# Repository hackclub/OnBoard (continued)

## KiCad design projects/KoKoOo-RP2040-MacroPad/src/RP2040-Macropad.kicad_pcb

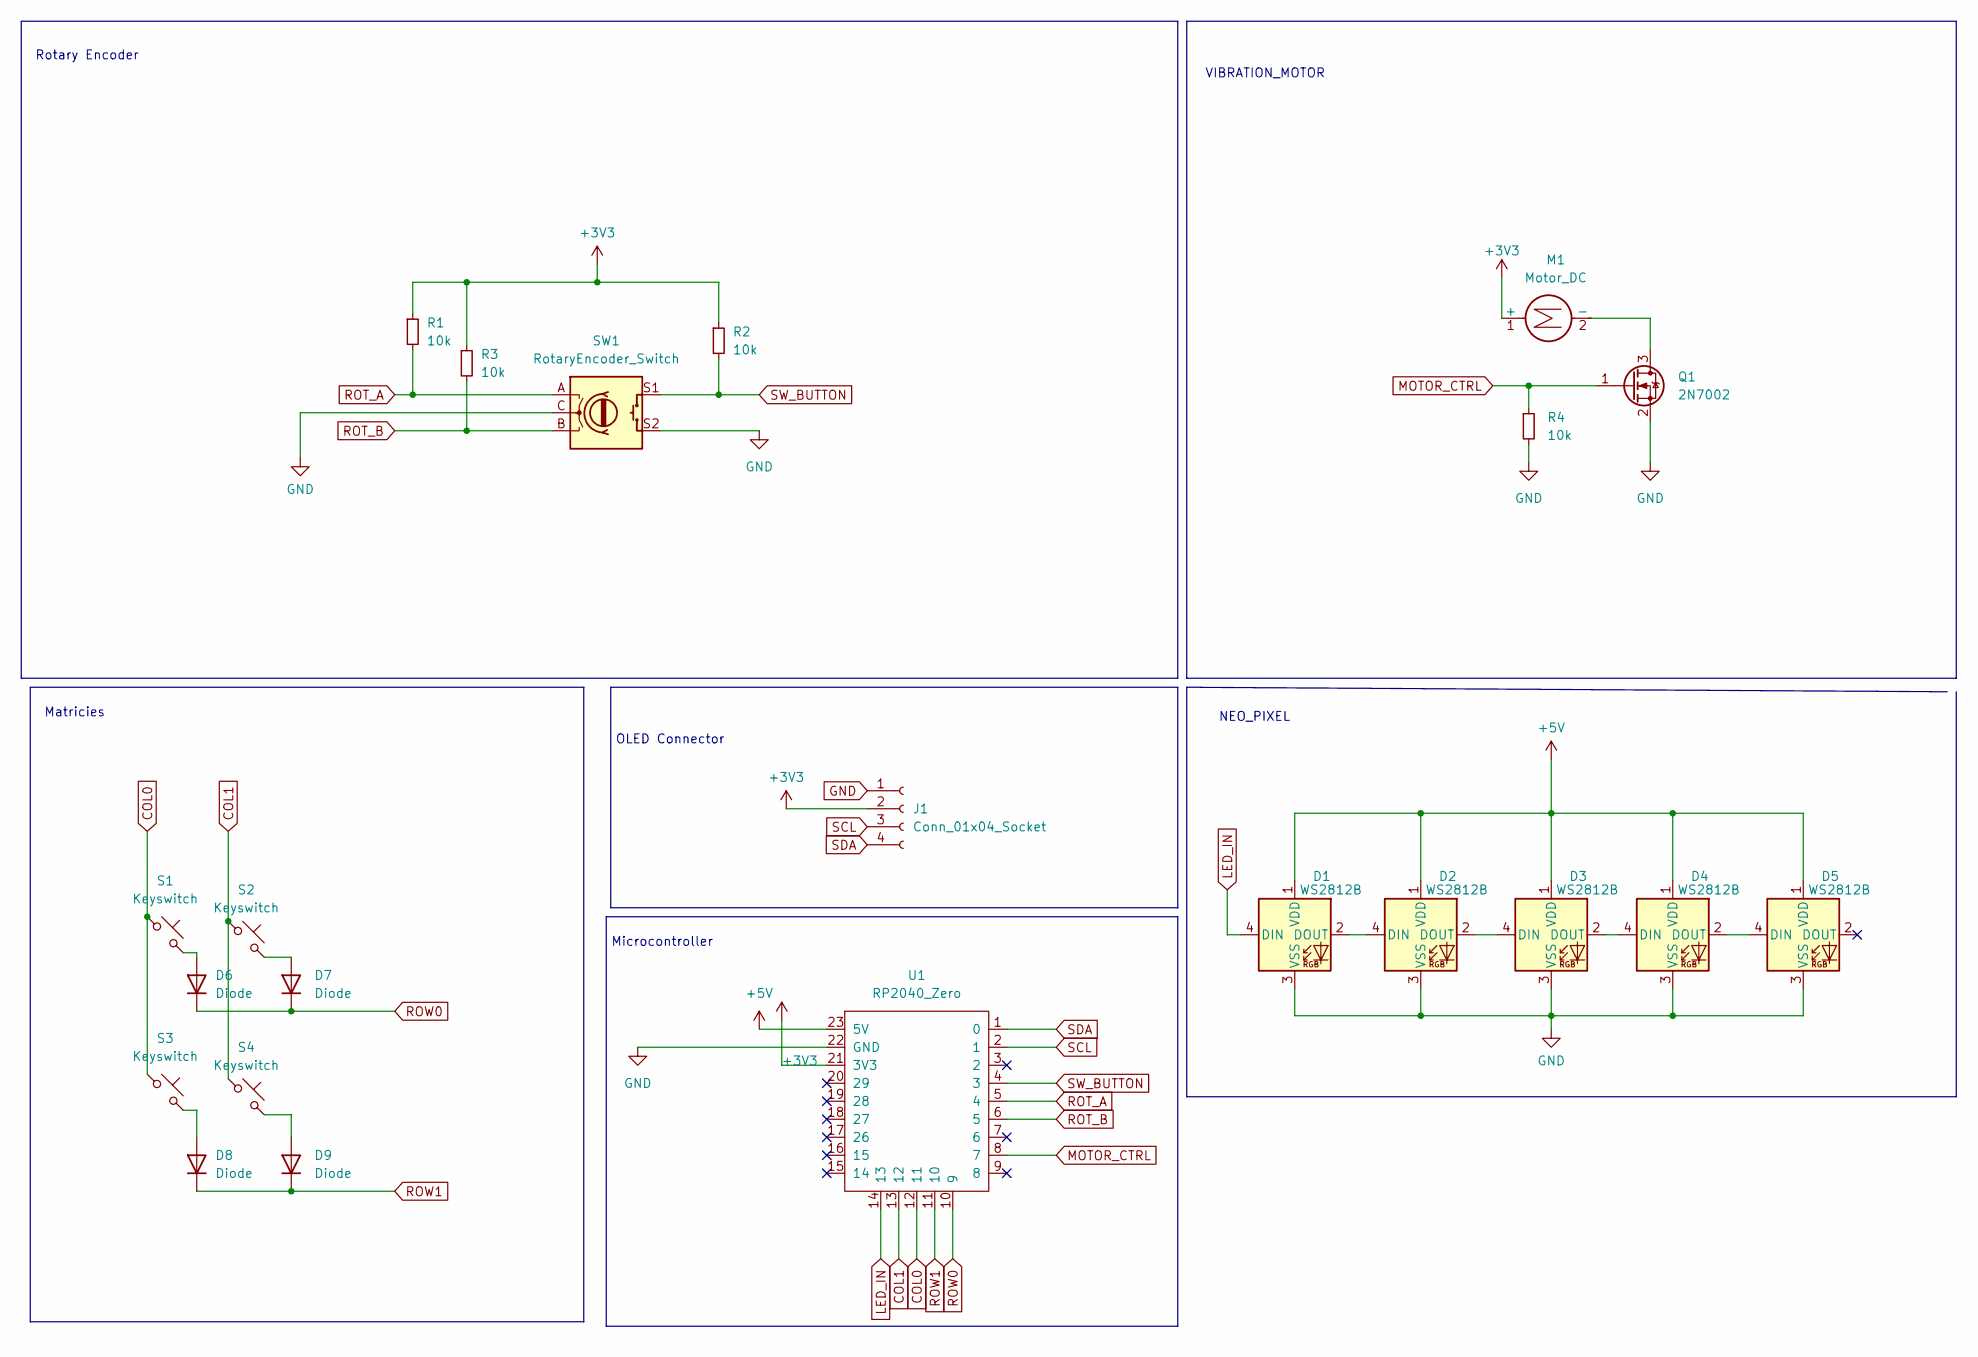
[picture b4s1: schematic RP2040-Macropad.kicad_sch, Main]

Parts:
D1, D2, D3, D4, D5: WS2812B; LED-WS2812BF5
D6, D7, D8, D9: Diode; Diode_SOD-123
J1: Conn_01x04_Socket; PinSocket_1x04_P2.54mm_Vertical
M1: Motor_DC; VC0820B006F
Q1: 2N7002; SOT-23
R1, R2, R3, R4: 10k; R_0805_2012Metric
S1, S2, S3, S4: Keyswitch; MX_Plate
SW1: RotaryEncoder_Switch; RotaryEncoder_Alps_EC11E-Switch_Vertical_H20mm
U1: RP2040_Zero

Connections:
+3V3: J1.2, M1.1 (+), R1.1, R2.1, R3.1, U1.21 (3V3)
+5V: D1.1 (VDD), D2.1 (VDD), D3.1 (VDD), D4.1 (VDD), D5.1 (VDD), U1.23 (5V)
COL0: S1.1, S3.1, U1.12 (11)
COL1: S2.1, S4.1, U1.13 (12)
GND: D1.3 (VSS), D2.3 (VSS), D3.3 (VSS), D4.3 (VSS), D5.3 (VSS), J1.1, Q1.2 (S), R4.2, SW1.C, SW1.S2, U1.22 (GND)
LED_IN: D1.4 (DIN), U1.14 (13)
MOTOR_CTRL: Q1.1 (G), R4.1, U1.8 (7)
unnamed: D1.2 (DOUT), D2.4 (DIN)
unnamed: D2.2 (DOUT), D3.4 (DIN)
unnamed: D3.2 (DOUT), D4.4 (DIN)
unnamed: D4.2 (DOUT), D5.4 (DIN)
unnamed: D6.2 (A), S1.2
unnamed: D7.2 (A), S2.2
unnamed: D8.2 (A), S3.2
unnamed: D9.2 (A), S4.2
unnamed: M1.2 (-), Q1.3 (D)
ROT_A: R1.2, SW1.A, U1.5 (4)
ROT_B: R3.2, SW1.B, U1.6 (5)
ROW0: D6.1 (K), D7.1 (K), U1.10 (9)
ROW1: D8.1 (K), D9.1 (K), U1.11 (10)
SCL: J1.3, U1.2 (1)
SDA: J1.4, U1.1 (0)
SW_BUTTON: R2.2, SW1.S1, U1.4 (3)

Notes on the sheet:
Matricies
NEO_PIXEL
Rotary Encoder
OLED Connector
Microcontroller
VIBRATION_MOTOR

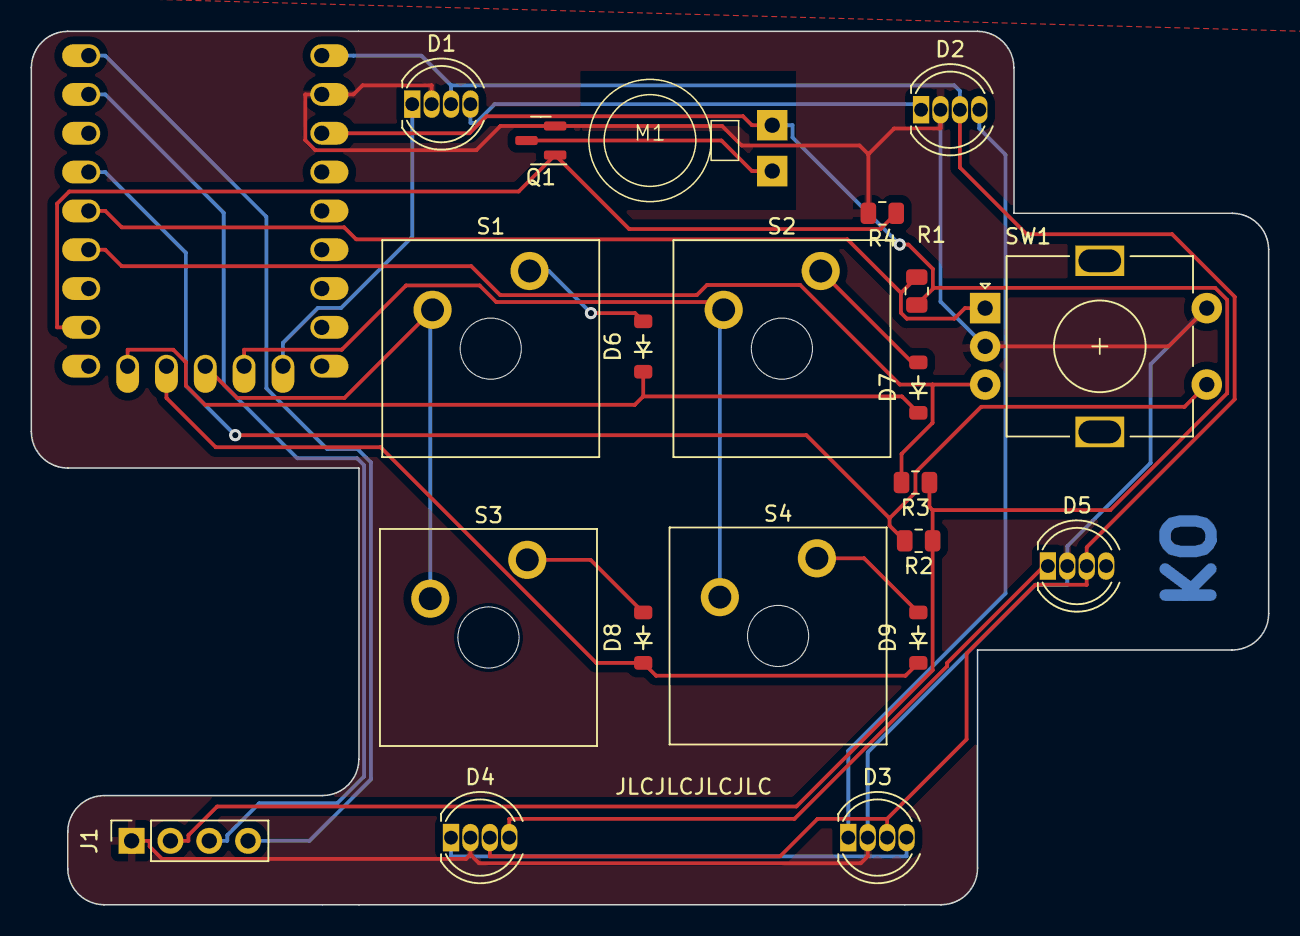
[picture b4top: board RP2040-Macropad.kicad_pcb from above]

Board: 2 copper layers, 81.0 x 57.2 mm, 22 parts (1 on the bottom side), 23 nets.

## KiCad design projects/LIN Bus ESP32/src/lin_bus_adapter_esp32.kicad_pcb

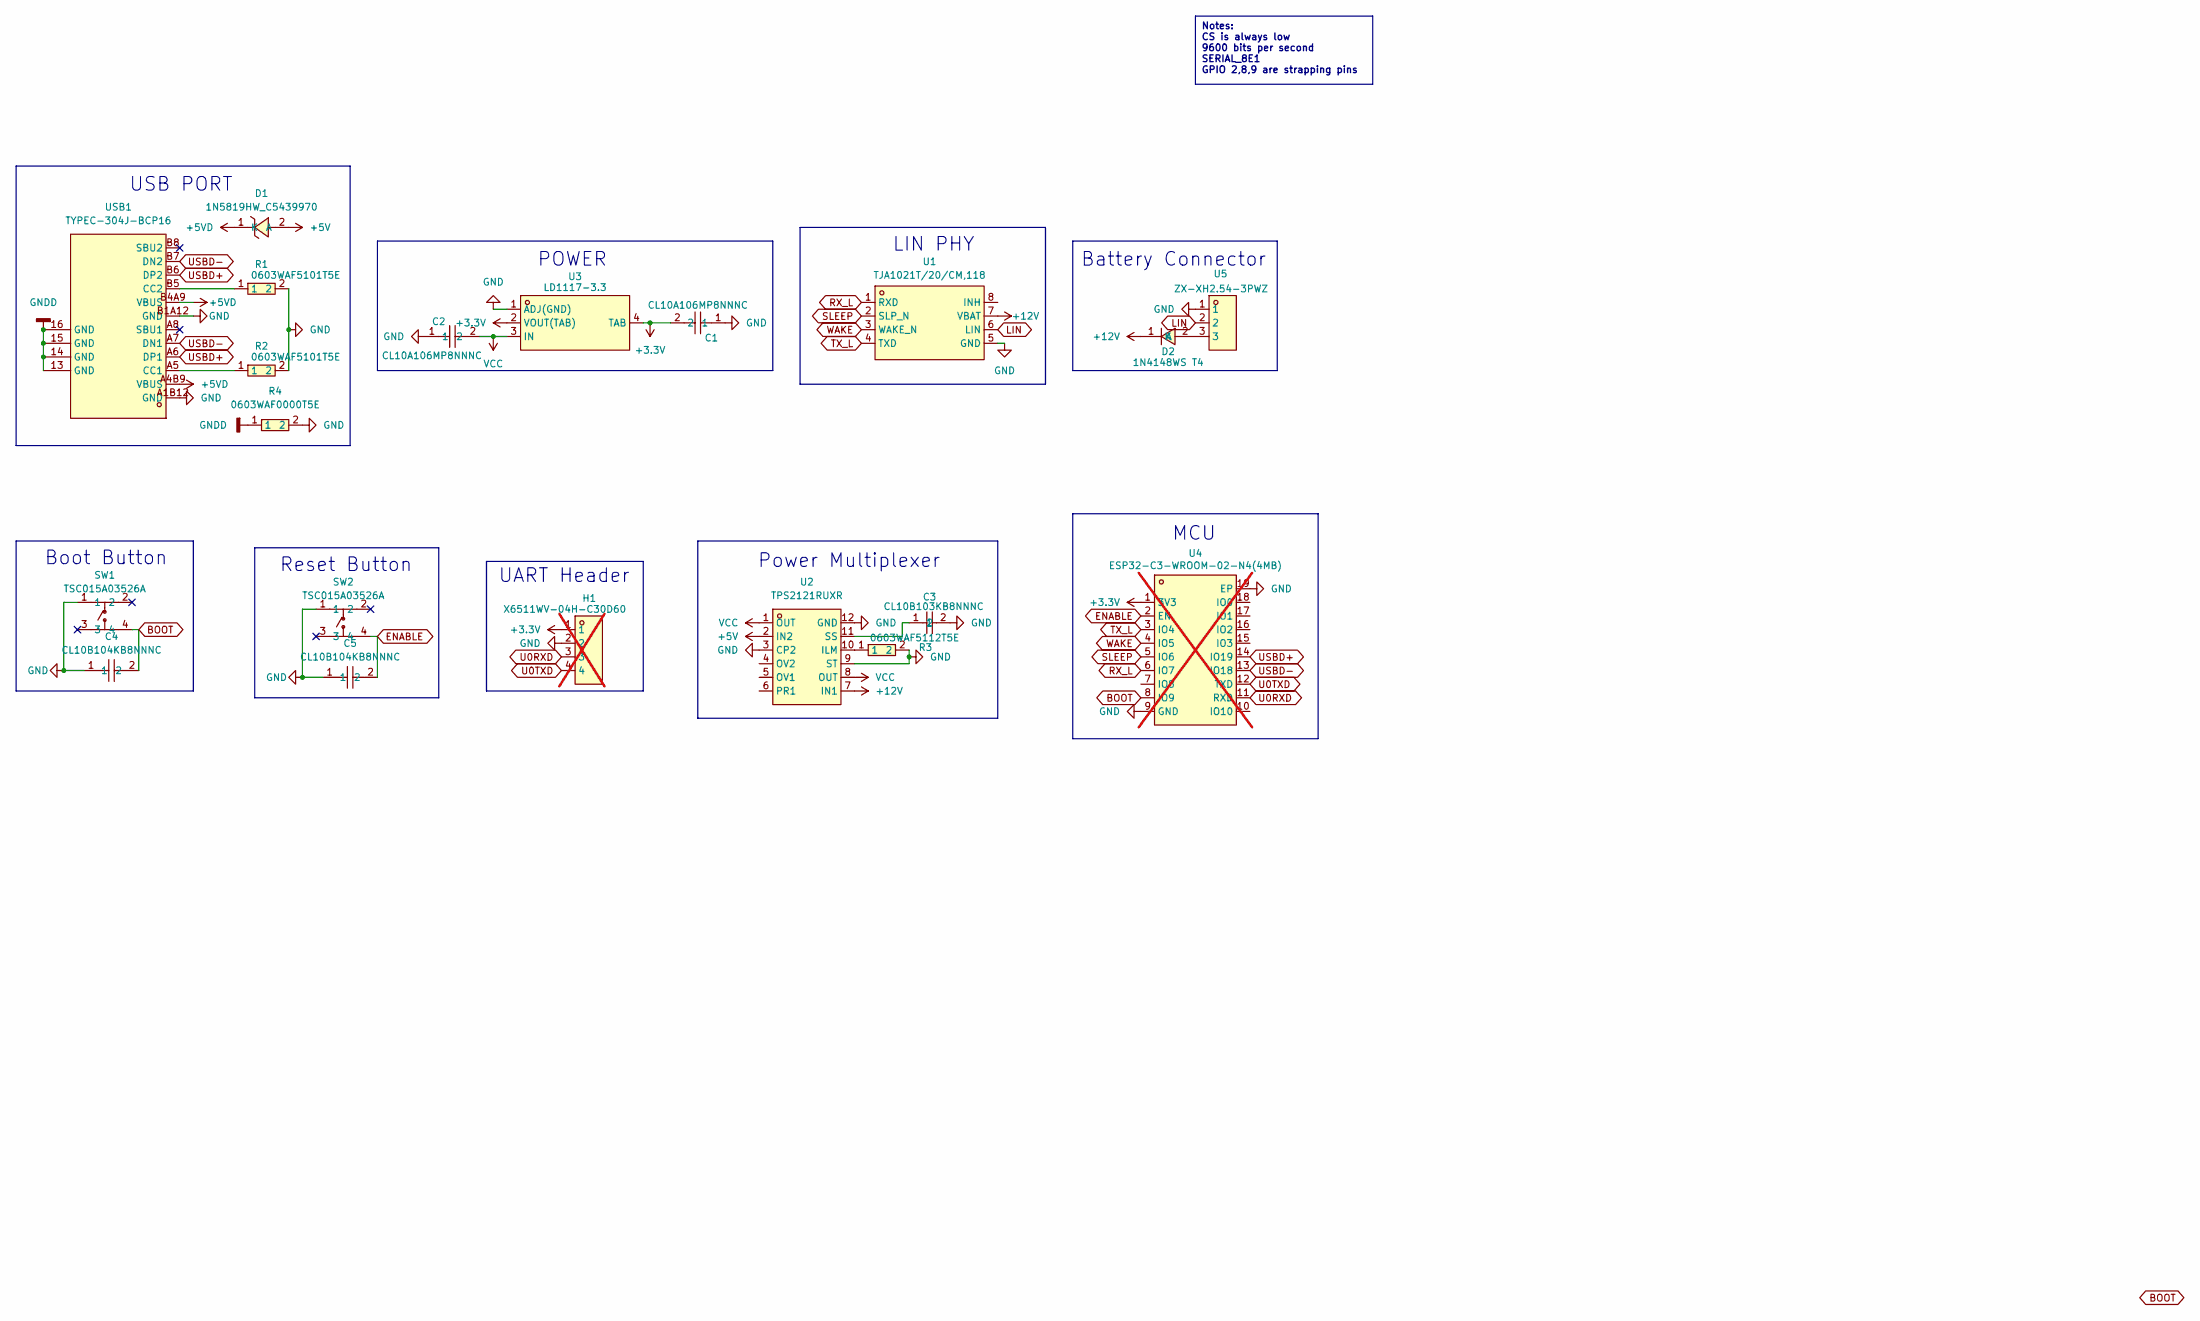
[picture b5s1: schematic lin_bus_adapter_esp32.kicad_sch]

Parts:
C1, C2: CL10A106MP8NNNC; C0603; LCSC Part C85713
C3: CL10B103KB8NNNC; C0603; LCSC Part C1589
C4, C5: CL10B104KB8NNNC; C0603; LCSC Part C1591
D1: 1N5819HW_C5439970; SOD-123_L2.7-W1.6-LS3.7-RD-1; LCSC Part C5439970
D2: 1N4148WS T4; SOD-323_L1.8-W1.3-LS2.5-RD; LCSC Part C2128
H1: X6511WV-04H-C30D60; HDR-TH_4P-P2.54-V-M; LCSC Part C706876; not fitted
R1, R2: 0603WAF5101T5E; R0603; LCSC Part C23186
R3: 0603WAF5112T5E; R0603; LCSC Part C23072
R4: 0603WAF0000T5E; R0603; LCSC Part C21189
SW1, SW2: TSC015A03526A; SW-SMD_4P-L4.5-W4.5-P3.00-LS6.8; LCSC Part C2888900
U1: TJA1021T/20/CM,118; SOIC-8_L4.9-W3.9-P1.27-LS6.0-BL; LCSC Part C128810
U2: TPS2121RUXR; VQFN-HR-12_L2.5-W2.0-P0.50-BL; LCSC Part C485916
U3: LD1117-3.3; SOT-223_L6.7-W3.5-P2.30-BR; LCSC Part C347229
U4: ESP32-C3-WROOM-02-N4(4MB); BULETM-SMD_ESPRESSIF_ESP32-C3-WROOM-02-N4-4MB; LCSC Part C2934560; not fitted
U5: ZX-XH2.54-3PWZ; HDR-TH_3P-P2.50_ZX-XH2.54-3PWZ; LCSC Part C7429642
USB1: TYPEC-304J-BCP16; USB-C-SMD_TYPEC-304J-BCP16; LCSC Part C2835315

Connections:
+3.3V: C1.2, H1.1, U3.2 (VOUT(TAB)), U3.4 (TAB), U4.1 (3V3)
+5V: D1.2 (A), U2.2 (IN2)
+5VD: D1.1 (K), USB1.A4B9 (VBUS), USB1.B4A9 (VBUS)
+12V: D2.1 (K), U1.7 (VBAT), U2.7 (IN1)
BOOT: C4.2, SW1.4, U4.8 (IO9)
ENABLE: C5.2, SW2.4, U4.2 (EN)
GND: C1.1, C2.1, C3.2, C4.1, C5.1, H1.2, R1.2, R2.2, R3.2, R4.2, SW1.1, SW2.1, U1.5 (GND), U2.3 (CP2), U2.9 (ST), U2.12 (GND), U3.1 (ADJ(GND)), U4.9 (GND), U4.19 (EP), U5.1, USB1.A1B12 (GND), USB1.B1A12 (GND)
GNDD: R4.1, USB1.13 (GND), USB1.14 (GND), USB1.15 (GND), USB1.16 (GND)
LIN: U1.6 (LIN), U5.2
unnamed: D2.2 (A), U5.3
unnamed: R3.1, U2.10 (ILM)
unnamed: C3.1, U2.11 (SS)
unnamed: R2.1, USB1.A5 (CC1)
unnamed: R1.1, USB1.B5 (CC2)
RX_L: U1.1 (RXD), U4.6 (IO7)
SLEEP: U1.2 (SLP_N), U4.5 (IO6)
TX_L: U1.4 (TXD), U4.3 (IO4)
U0RXD: H1.3, U4.11 (RXD)
U0TXD: H1.4, U4.12 (TXD)
USBD+: U4.14 (IO19), USB1.A6 (DP1), USB1.B6 (DP2)
USBD-: U4.13 (IO18), USB1.A7 (DN1), USB1.B7 (DN2)
VCC: C2.2, U2.1 (OUT), U2.8 (OUT), U3.3 (IN)
WAKE: U1.3 (WAKE_N), U4.4 (IO5)

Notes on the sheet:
Notes: CS is always low 9600 bits per second SERIAL_8E1 GPIO 2,8,9 are strapping pins
Power Multiplexer
Battery Connector
Reset Button
Boot Button
LIN PHY
USB PORT
POWER
MCU
UART Header

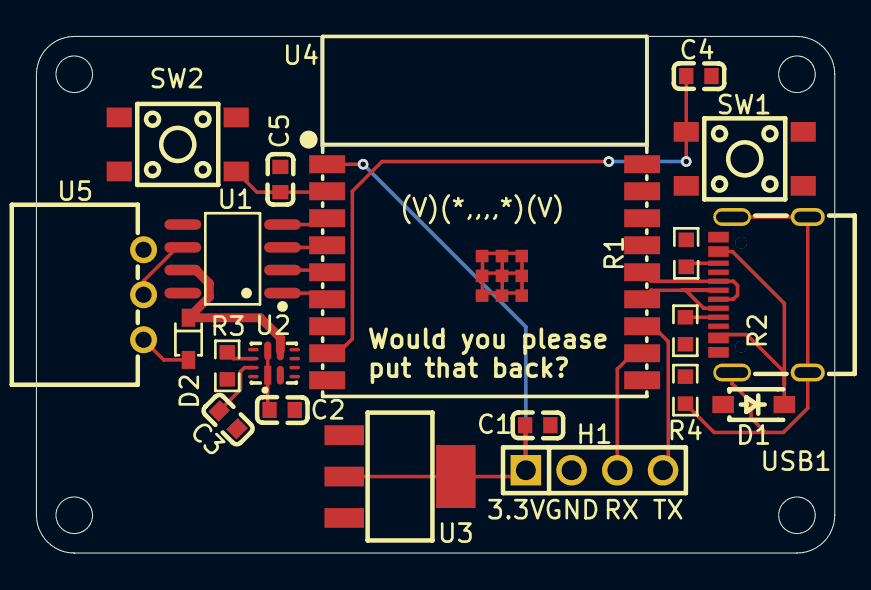
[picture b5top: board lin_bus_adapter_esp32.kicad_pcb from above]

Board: 2 copper layers, 44.3 x 28.7 mm, 20 parts (0 on the bottom side), 23 nets.

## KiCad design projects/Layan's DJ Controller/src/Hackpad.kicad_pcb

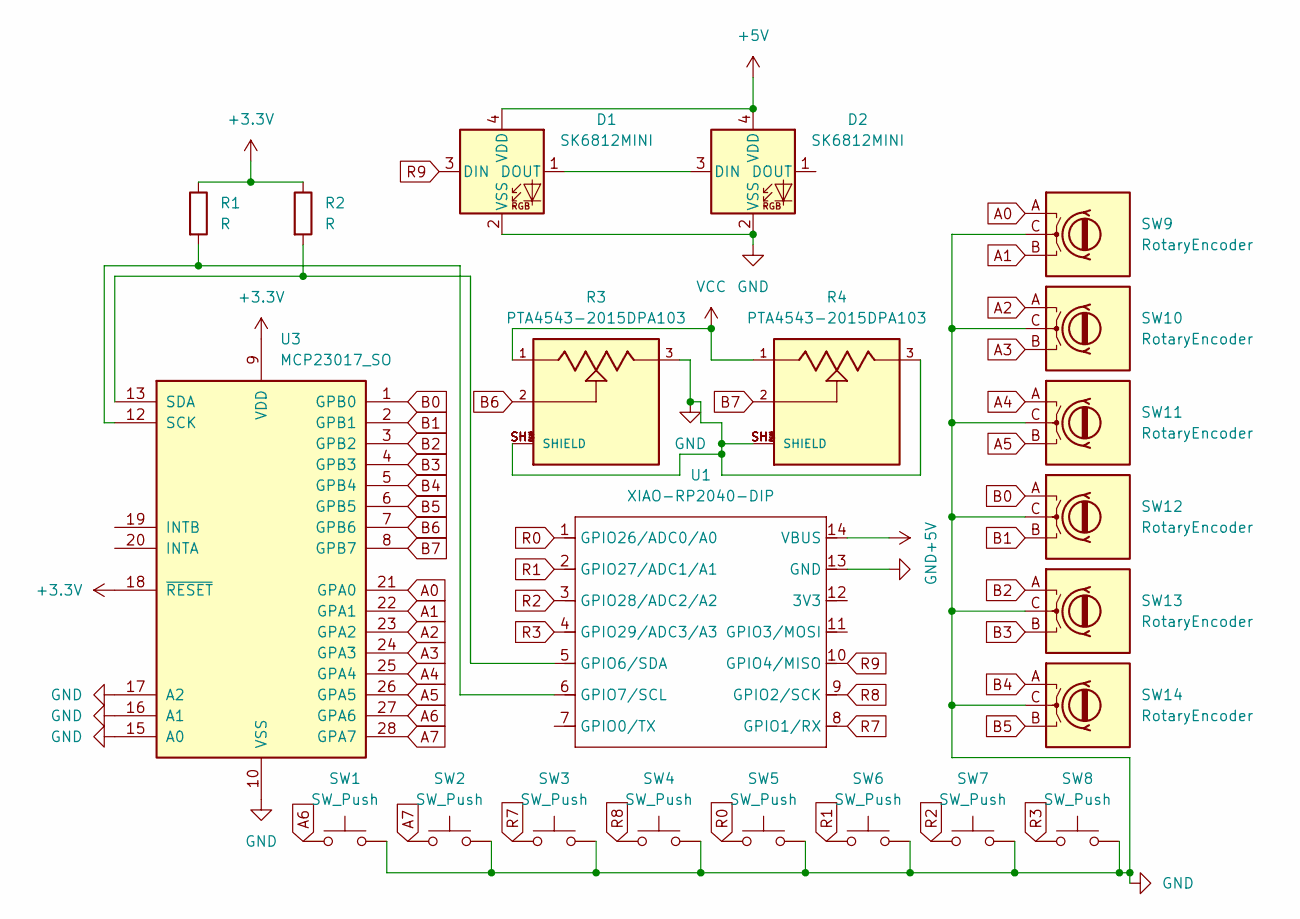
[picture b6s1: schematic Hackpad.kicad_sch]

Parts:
D1, D2: SK6812MINI; LED_SK6812MINI_PLCC4_3.5x3.5mm_P1.75mm; LCSC C5149201
R1, R2: R; R_Axial_DIN0204_L3.6mm_D1.6mm_P7.62mm_Horizontal; LCSC C3151642
R3, R4: PTA4543-2015DPA103; TRIM_PTA4543-2015DPA103; PARTREV 04/21; LCSC C17328789
SW1, SW2, SW3, SW4, SW5, SW6, SW7, SW8: SW_Push; SW_Cherry_MX_1.00u_PCB; LCSC C3316924
SW9, SW10, SW11, SW12, SW13, SW14: RotaryEncoder; RotaryEncoder_Alps_EC11E_Vertical_H20mm; LCSC C470710
U1: XIAO-RP2040-DIP; LCSC C9900176459
U3: MCP23017_SO; SOIC-28W_7.5x17.9mm_P1.27mm; LCSC C47023

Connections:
+3.3V: R1.1, R2.1, U3.9 (VDD), U3.18 (~RESET)
+5V: D1.4 (VDD), D2.4 (VDD), U1.14 (VBUS)
A0: SW9.A, U3.21 (GPA0)
A1: SW9.B, U3.22 (GPA1)
A2: SW10.A, U3.23 (GPA2)
A3: SW10.B, U3.24 (GPA3)
A4: SW11.A, U3.25 (GPA4)
A5: SW11.B, U3.26 (GPA5)
A6: SW1.1, U3.27 (GPA6)
A7: SW2.1, U3.28 (GPA7)
B0: SW12.A, U3.1 (GPB0)
B1: SW12.B, U3.2 (GPB1)
B2: SW13.A, U3.3 (GPB2)
B3: SW13.B, U3.4 (GPB3)
B4: SW14.A, U3.5 (GPB4)
B5: SW14.B, U3.6 (GPB5)
B6: R3.2, U3.7 (GPB6)
B7: R4.2, U3.8 (GPB7)
GND: D1.2 (VSS), D2.2 (VSS), R3.3, R3.SH1 (SHIELD), R3.SH2 (SHIELD), R3.SH3 (SHIELD), R3.SH4 (SHIELD), R4.3, R4.SH1 (SHIELD), R4.SH2 (SHIELD), R4.SH3 (SHIELD), R4.SH4 (SHIELD), SW1.2, SW2.2, SW3.2, SW4.2, SW5.2, SW6.2, SW7.2, SW8.2, SW9.C, SW10.C, SW11.C, SW12.C, SW13.C, SW14.C, U1.13 (GND), U3.10 (VSS), U3.15 (A0), U3.16 (A1), U3.17 (A2)
unnamed: D1.1 (DOUT), D2.3 (DIN)
unnamed: R2.2, U1.5 (GPIO6/SDA), U3.13 (SDA)
unnamed: R1.2, U1.6 (GPIO7/SCL), U3.12 (SCK)
R0: SW5.1, U1.1 (GPIO26/ADC0/A0)
R1: SW6.1, U1.2 (GPIO27/ADC1/A1)
R2: SW7.1, U1.3 (GPIO28/ADC2/A2)
R3: SW8.1, U1.4 (GPIO29/ADC3/A3)
R7: SW3.1, U1.8 (GPIO1/RX)
R8: SW4.1, U1.9 (GPIO2/SCK)
R9: D1.3 (DIN), U1.10 (GPIO4/MISO)
VCC: R3.1, R4.1

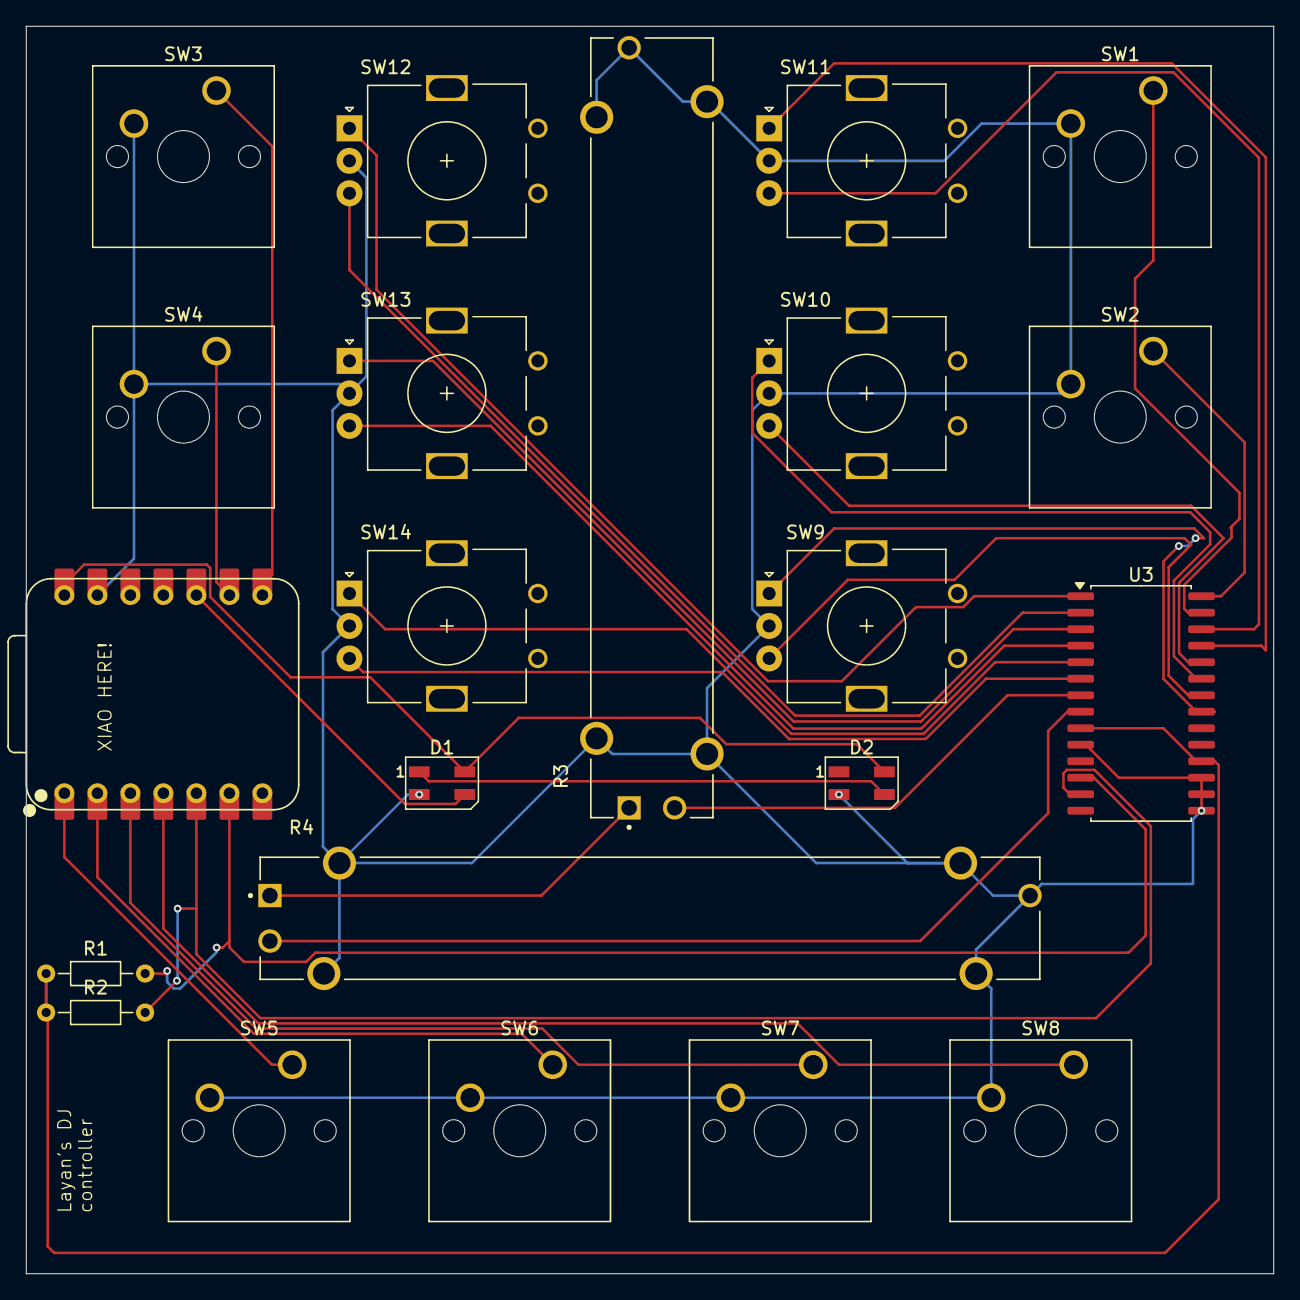
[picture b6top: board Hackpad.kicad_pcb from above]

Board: 2 copper layers, 96.0 x 96.0 mm, 22 parts (0 on the bottom side), 30 nets.
